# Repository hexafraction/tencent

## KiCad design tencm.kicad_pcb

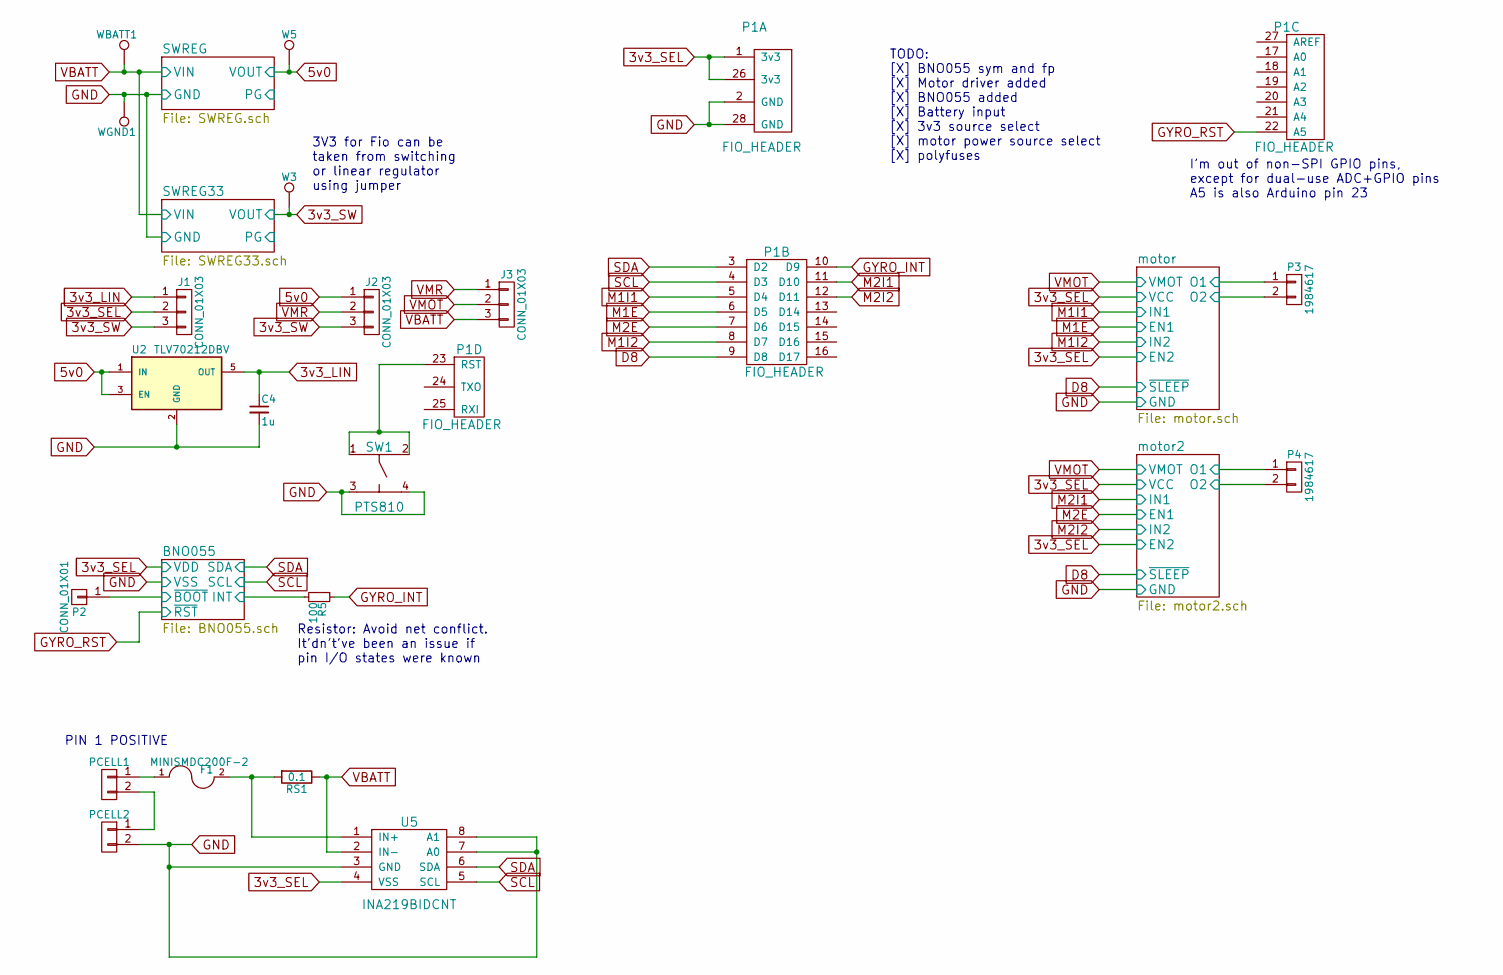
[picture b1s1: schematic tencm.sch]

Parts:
C4: 1u; C_0603
F1: MINISMDC200F-2; R_1812_HandSoldering
J1, J2, J3: CONN_01X03; Pin_Header_Straight_1x03
P1: FIO_HEADER; FIO_DIP
P2: CONN_01X01; Pin_Header_Straight_1x01
P3, P4: 1984617; TerminalBlock_Pheonix_PT-3.5mm_2pol
PCELL1, PCELL2: S2B-PH-K-S(LF)(SN); Connectors_JST_S2B-PH-K
R5: 100; R_0603
RS1: 0.1; MF_Passives-R1206
SW1: PTS810; BTN_PTS_810
U2: TLV70212DBV; MF_IC_Power-SOT-23-5
U5: INA219BIDCNT; sot23-8
W3, W5: TEST_1P; Measurement_Point_Round-TH_Small
WBATT1: TEST_1P; Measurement_Point_Round-TH_Small
WGND1: TEST_1P; Measurement_Point_Round-TH_Small

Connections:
3v3_LIN: C4.1, J1.1, U2.5 (OUT)
3v3_SEL: J1.2, P1.1 (3v3), P1.26 (3v3), U5.4 (VSS); also elsewhere on the board
3v3_SW: J1.3, J2.3, W3.1; also elsewhere on the board
5v0: J2.1, U2.1 (IN), U2.3 (EN), W5.1; also elsewhere on the board
/BNO055/INT: R5.2; also elsewhere on the board
/BNO055/~BOOT: P2.1; also elsewhere on the board
/motor2/O1: P4.1; also elsewhere on the board
/motor2/O2: P4.2; also elsewhere on the board
/motor/O1: P3.1; also elsewhere on the board
/motor/O2: P3.2; also elsewhere on the board
D8: P1.9 (D8); also elsewhere on the board
GGND: C4.2, P1.2 (GND), P1.28 (GND), PCELL2.2, SW1.3, SW1.4, U2.2 (GND), U5.3 (GND), U5.7 (A0), U5.8 (A1), WGND1.1; also elsewhere on the board
GRST: P1.22 (A5); also elsewhere on the board
GYRO_INT: P1.10 (D9), R5.1
M1E: P1.6 (D5); also elsewhere on the board
M1I1: P1.5 (D4); also elsewhere on the board
M1I2: P1.8 (D7); also elsewhere on the board
M2E: P1.7 (D6); also elsewhere on the board
M2I1: P1.11 (D10); also elsewhere on the board
M2I2: P1.12 (D11); also elsewhere on the board
unnamed: F1.1, PCELL1.1
unnamed: F1.2, RS1.2, U5.1 (IN+)
unnamed: P1.23 (RST), SW1.1, SW1.2
unnamed: PCELL1.2, PCELL2.1
SCL: P1.4 (D3), U5.5 (SCL); also elsewhere on the board
SDA: P1.3 (D2), U5.6 (SDA); also elsewhere on the board
VBATT: J3.3, RS1.1, U5.2 (IN-), WBATT1.1; also elsewhere on the board
VMOT: J3.2; also elsewhere on the board
VMR: J2.2, J3.1

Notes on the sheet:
3V3 for Fio can be taken from switching or linear regulator using jumper
TODO: [X] BNO055 sym and fp [X] Motor driver added [X] BNO055 added [X] Battery input [X] 3v3 source select [X] motor power source select [X] polyfuses
Resistor: Avoid net conflict. It'dn't've been an issue if pin I/O states were known
PIN 1 POSITIVE
I'm out of non-SPI GPIO pins, except for dual-use ADC+GPIO pins A5 is also Arduino pin 23

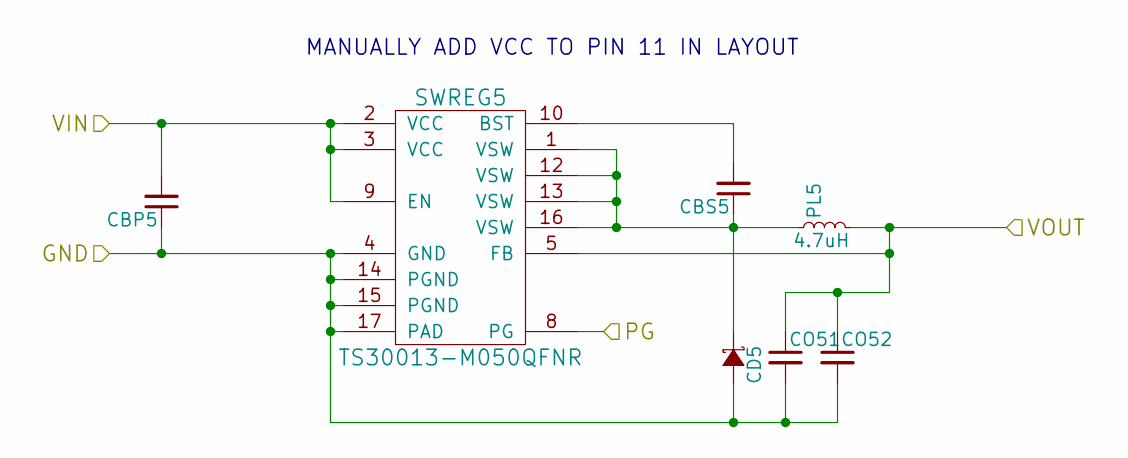
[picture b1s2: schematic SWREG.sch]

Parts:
CBP5: GMK316F106ZL-T; C_1206
CBS5: GMK316F106ZL-T; C_1206
CD5: PMEG4050EP; SOD128
CO51, CO52: CC0603MRX5R5BB226; C_0603
PL5: 4.7uH; L_5040
SWREG5: TS30013-M050QFNR; QFN16_TS30013

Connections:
5v0: CO51.1, CO52.1, PL5.2, SWREG5.5 (FB); also elsewhere on the board
/SWREG/PG: SWREG5.8 (PG)
GGND: CBP5.1, CD5.2 (A), CO51.2, CO52.2, SWREG5.4 (GND), SWREG5.14 (PGND), SWREG5.15 (PGND), SWREG5.17 (PAD); also elsewhere on the board
unnamed: CBS5.1, CD5.1 (K), PL5.1, SWREG5.1 (VSW), SWREG5.12 (VSW), SWREG5.13 (VSW), SWREG5.16 (VSW)
unnamed: CBS5.2, SWREG5.10 (BST)
VBATT: CBP5.2, SWREG5.2 (VCC), SWREG5.3 (VCC), SWREG5.9 (EN), SWREG5.11; also elsewhere on the board

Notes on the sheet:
MANUALLY ADD VCC TO PIN 11 IN LAYOUT

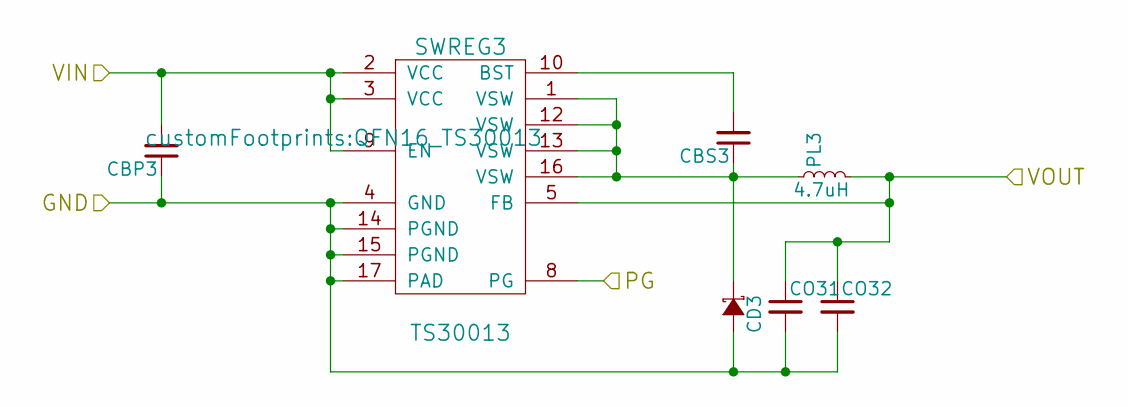
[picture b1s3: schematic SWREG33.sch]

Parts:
CBP3: GMK316F106ZL-T; C_1206
CBS3: GMK316F106ZL-T; C_1206
CD3: PMEG4050EP; SOD128
CO31, CO32: CC0603MRX5R5BB226; C_0603
PL3: 4.7uH; L_5040
SWREG3: TS30013; QFN16_TS30013

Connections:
3v3_SW: CO31.1, CO32.1, PL3.2, SWREG3.5 (FB); also elsewhere on the board
/SWREG33/PG: SWREG3.8 (PG)
GGND: CBP3.1, CD3.2 (A), CO31.2, CO32.2, SWREG3.4 (GND), SWREG3.14 (PGND), SWREG3.15 (PGND), SWREG3.17 (PAD); also elsewhere on the board
unnamed: CBS3.1, CD3.1 (K), PL3.1, SWREG3.1 (VSW), SWREG3.12 (VSW), SWREG3.13 (VSW), SWREG3.16 (VSW)
unnamed: CBS3.2, SWREG3.10 (BST)
VBATT: CBP3.2, SWREG3.2 (VCC), SWREG3.3 (VCC), SWREG3.9 (EN), SWREG3.11; also elsewhere on the board

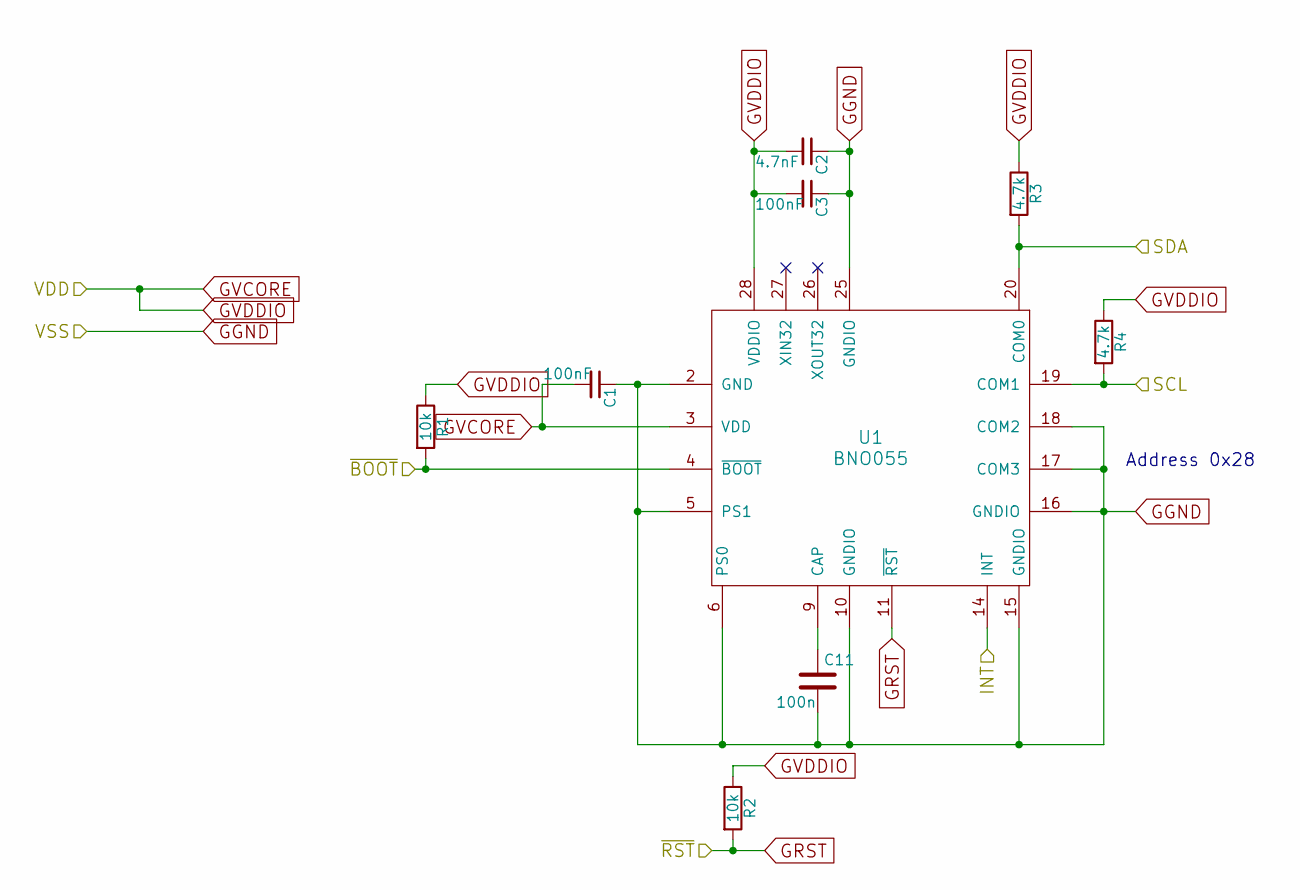
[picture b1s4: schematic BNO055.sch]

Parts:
C1, C3: 100nF; C_0603
C2: 4.7nF; C_0603
C11: 100n; C_0603
R1, R2: 10k; R_0603
R3, R4: 4.7k; R_0603
U1: BNO055; BNO055-SOIC

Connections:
3v3_SEL: C1.2, C2.2, C3.2, R1.1, R2.1, R3.1, R4.1, U1.3 (VDD), U1.28 (VDDIO); also elsewhere on the board
/BNO055/INT: U1.14 (INT); also elsewhere on the board
/BNO055/~BOOT: R1.2, U1.4 (~BOOT); also elsewhere on the board
GGND: C1.1, C2.1, C3.1, C11.2, U1.2 (GND), U1.5 (PS1), U1.6 (PS0), U1.10 (GNDIO), U1.15 (GNDIO), U1.16 (GNDIO), U1.17 (COM3), U1.18 (COM2), U1.25 (GNDIO); also elsewhere on the board
GRST: R2.2, U1.11 (~RST); also elsewhere on the board
unnamed: C11.1, U1.9 (CAP)
SCL: R4.2, U1.19 (COM1); also elsewhere on the board
SDA: R3.2, U1.20 (COM0); also elsewhere on the board

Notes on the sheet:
Address 0x28

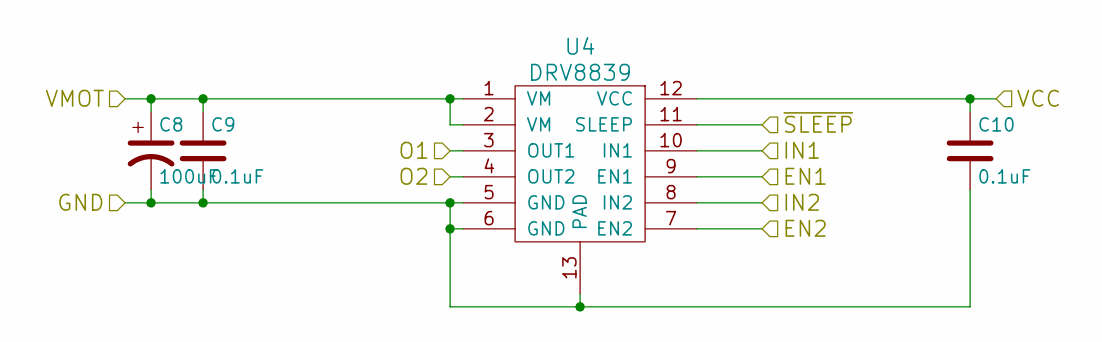
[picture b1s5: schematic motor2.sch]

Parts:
C8: 100uF; c_elec_5x5.3
C9, C10: 0.1uF; C_0603
U4: DRV8839; SOIC-12-DRV8839

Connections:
3v3_SEL: C10.1, U4.7 (EN2), U4.12 (VCC); also elsewhere on the board
/motor2/O1: U4.3 (OUT1); also elsewhere on the board
/motor2/O2: U4.4 (OUT2); also elsewhere on the board
D8: U4.11 (SLEEP); also elsewhere on the board
GGND: C8.2, C9.2, C10.2, U4.5 (GND), U4.6 (GND), U4.13 (PAD); also elsewhere on the board
M2E: U4.9 (EN1); also elsewhere on the board
M2I1: U4.10 (IN1); also elsewhere on the board
M2I2: U4.8 (IN2); also elsewhere on the board
VMOT: C8.1, C9.1, U4.1 (VM), U4.2 (VM); also elsewhere on the board

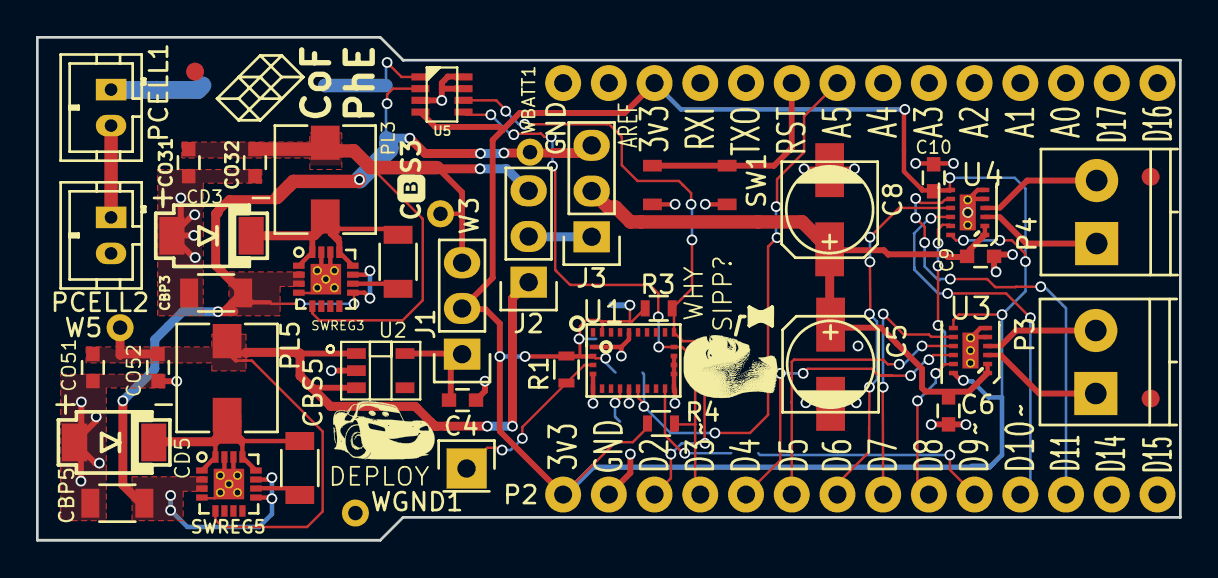
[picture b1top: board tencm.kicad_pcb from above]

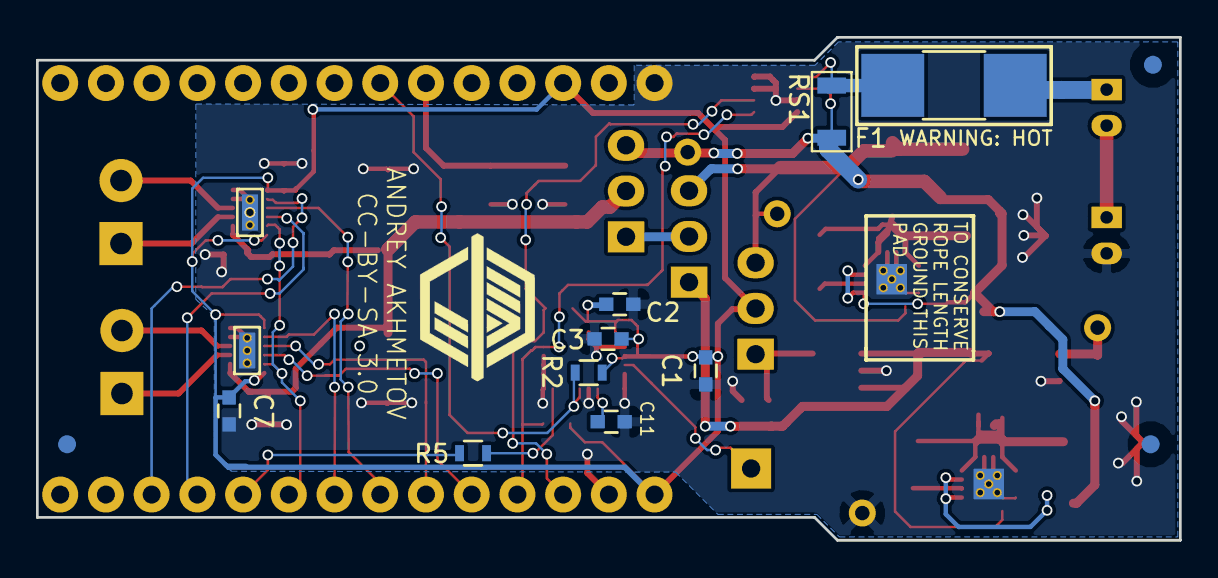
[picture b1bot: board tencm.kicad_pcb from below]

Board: 2 copper layers, 63.5 x 27.9 mm, 57 parts (12 on the bottom side), 34 nets.

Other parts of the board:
C5: 100uF; c_elec_5x5.3
C6, C7: 0.1uF; C_0603
FID1, FID2, FID3, FID4, FID5, FID6: Fiducial_1mm_Dia_2.54mm_Outer_CopperTop
U3: DRV8839; SOIC-12-DRV8839

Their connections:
3v3_SEL: C7.1, U3.7, U3.12; also elsewhere on the board
/motor/O1: U3.3; also elsewhere on the board
/motor/O2: U3.4; also elsewhere on the board
D8: U3.11; also elsewhere on the board
GGND: C5.2, C6.2, C7.2, U3.5, U3.6, U3.13; also elsewhere on the board
M1E: U3.9; also elsewhere on the board
M1I1: U3.10; also elsewhere on the board
M1I2: U3.8; also elsewhere on the board
VMOT: C5.1, C6.1, U3.1, U3.2; also elsewhere on the board

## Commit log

2017-06-13 Initial commit.
2017-06-18 lots of work on schematic
2017-06-19 initiial layout
2017-06-22 board v1

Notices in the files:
tencm.kicad_pcb:
CC-BY-SA 3.0
